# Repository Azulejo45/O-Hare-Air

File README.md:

# ┕━━O-Hare-Air━━┙ 
- Proyecto de sistema de ventilación automatizado y controlado por ESP32-C3 Super Mini. Equipado con control PWM mediante MOSFET, sensor de temperatura DS18B20 y regulación de voltaje eficiente.

### -----〈 Autores  〉-----\

> ⋆ˊˎ-Velazquez Joaquim

 ---30/09/2026---
\
\
\
### •---Especificaciones generales 
\
˚₊· ͟͟͞͞  Control de velocidad: PWM por MOSFET (IRLZ44N).\

˚₊· ͟͟͞͞  Alimentación principal: 12V / 2A (Entrada Jack DC).\

˚₊· ͟͟͞͞  Regulación interna: 5V mediante módulo Mini360.\

˚₊· ͟͟͞͞  Material de la estructura/gabinete: PLA.

_____________________________ \
\
\
.
### Objetivo del proyecto
\
El objetivo principal de este proyecto es diseñar e implementar un sistema de ventilación inteligente regulado por temperatura. Utilizando un microcontrolador ESP32-C3 Super Mini, una etapa de potencia con MOSFET y un sensor DS18B20, el sistema ajusta dinámicamente las revoluciones del ventilador de forma automática para mantener una temperatura óptima de manera eficiente.

# ⌒⌒⌒⌒⌒⌒⌒⌒┈୨•୧┈⌒⌒⌒⌒⌒⌒⌒⌒
\
\
\
\
### ˗ˏˋ ꒰ Este proyecto fue realizado con algunos componentes en donde se puede llegan a encontrar: ꒱ ˎˊ˗

 -  ESP32-C3 Super Mini.

> Memoria: 400 KB SRAM, 4 MB Flash. Conectividad: Wi-Fi (2,4 GHz).

> Bluetooth 5.0 LE (Low Energy).

> Alimentación: Funciona a 3,3 V con entrada USB-C de 5 V.

- Sensor de Temperatura: DS18B20 (KY-001).

> Voltaje de operación: 3.0V - 5.5V.

> Rango de medición: -55°C a +125°C.

-  MOSFET de Potencia: IRLZ44N.

> Tipo: Canal N (Logic-Level).

> Voltaje Drain-Source max: 55V.

> Corriente continua de Drain: 47A.

- Diodo de protección: 1N4007.

> Uso: Diodo flyback en antiparalelo con el motor para suprimir picos inductivos.

- Regulador de voltaje: Módulo Mini360.

> Tipo: Step-Down Buck Converter.

> Voltaje de entrada: 4.75V - 23V.

> Voltaje de salida ajustable: 5V.

- WS2812 (tira led x12)

> Tipo: RGB

> Uso: proyección de imagenes en el aspa

- Sensor de efecto Hall

> Uso: Medición de los rpms del motor para ayudar  los WS2812

> Alimentción: 5v con un división de tensión 3.3v para la señal de retorno

\
\
\
\
.
## ╔════╡Componentes utilizados╞════╗
➸ ESP32-C3 Super Mini.

➸ Sensor DS18B20.

➸ MOSFET IRLZ44N.

➸ Diodo 1N4007.

➸ Módulo Mini360 (Step-Down 5V).

➸ Jack DC y Borneras de conexión.

➸ Leds WS2812 (x12)

➸ Sensor efecto Hall
\
\
\
.
## Diseños de los circuitos

\

### Descripcion del funcionamiento
\
El sistema monitorea de manera constante la temperatura ambiental o del componente a través del sensor DS18B20 conectado al ESP32-C3. Mediante un algoritmo de control, el microcontrolador varía el ciclo de trabajo de la señal PWM aplicada a la compuerta (Gate) del MOSFET IRLZ44N.
De esta forma, la velocidad del ventilador de 12V aumenta o disminuye de forma proporcional a la temperatura registrada, garantizando una disipación eficiente y un funcionamiento automatizado. El diodo 1N4007 protege al circuito de las corrientes inversas generadas por el motor al apagarse o variar su velocidad.

## Esquematicos

## Layouts de PCBs

\

## Pasos a seguir para el armado del sistema

### -|Soldar los componentes en la PCB en el siguiente orden recomendado:

1. Resistencias y diodos SMD/THT (incluyendo el diodo 1N4007).

2. Borneras de conexión y Jack DC.

3. Módulo Mini360 (previamente calibrado a 5V de salida).

4. Zócalos o pines para el ESP32-C3 Super Mini y el MOSFET.

# Medidas de seguridad.
- .°-> Verifique la polaridad de la fuente de alimentación de 12V antes de conectarla al Jack DC para evitar daños en los reguladores.

-.°-> Asegúrese de que el diodo 1N4007 esté correctamente orientado (con el cátodo apuntando hacia la línea positiva de alimentación del motor).

 # -|Gabinete y Montaje 3D
Descargar el modelo 3D del soporte o gabinete ubicado en la carpeta de HARDWARE.

- Imprimir la pieza en PLA.

- Ensamblar la placa de circuito impreso dentro de la estructura junto con el ventilador y el sensor DS18B20 en la zona de medición.

## -|Código y Firmware
El código establece las lecturas del sensor de temperatura y calcula la salida PWM necesaria para gobernar el MOSFET.

Principales tareas del programa:
.°-> Lectura periódica de temperatura mediante la librería 1-Wire / DallasTemperature.
.°-> Mapeo de la temperatura leída a un rango de ciclo de trabajo PWM (0% a 100%).
.°-> Aplicación de la señal de control hacia el pin correspondiente del ESP32-C3.

## -|Compilacion/Carga
Utilice un cable USB tipo C para conectar el ESP32-C3 a un ordenador. Se recomienda utilizar el entorno de desarrollo PlatformIO o Arduino IDE.\

- Seleccione la placa ESP32-C3 Dev Module (o Super Mini equivalente) y el puerto COM correspondiente.\

- Verifique que estén instaladas las librerías necesarias para el manejo del sensor de temperatura.\

- Compile y cargue el código en el microcontrolador.

## -[Librerías principales
OneWire

DallasTemperature

## -[Datasheets/Referencias

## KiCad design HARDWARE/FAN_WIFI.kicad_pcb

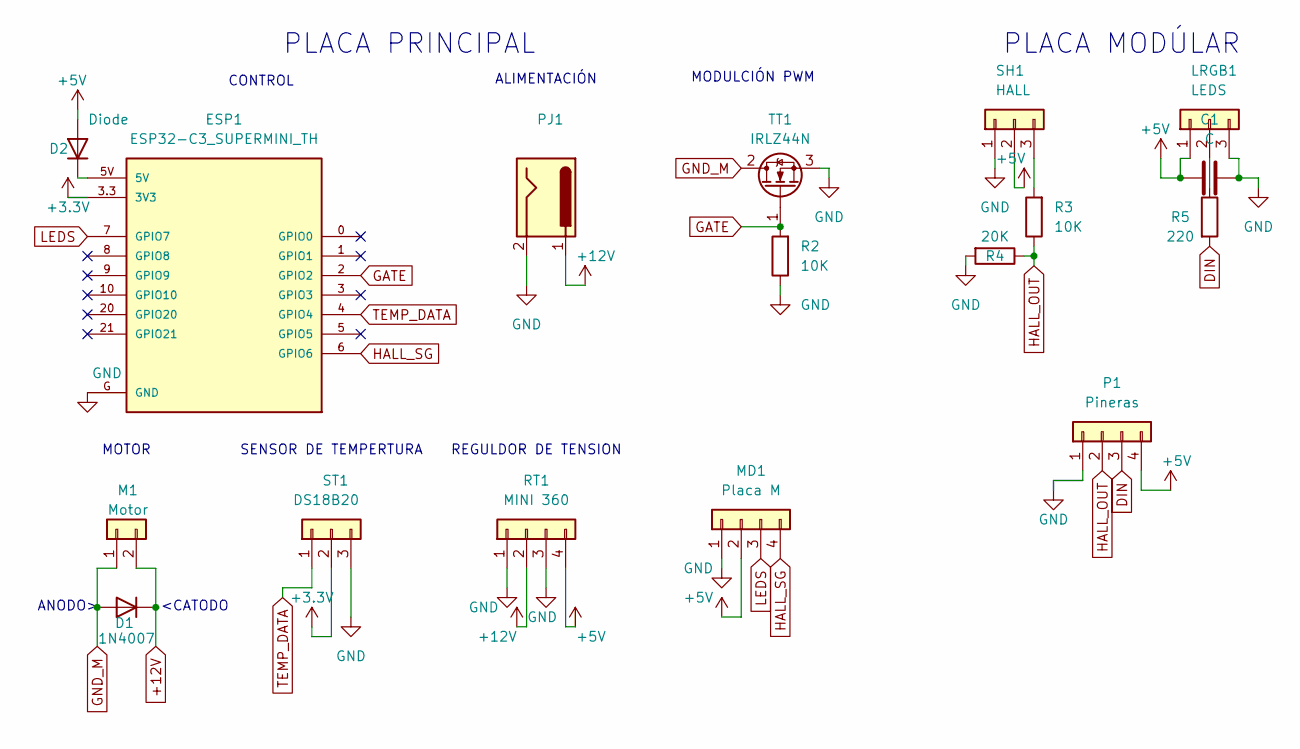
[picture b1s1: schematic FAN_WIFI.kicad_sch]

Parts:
C1: C; C_Disc_D5.0mm_W2.5mm_P5.00mm
D1: 1N4007; D_DO-41_SOD81_P10.16mm_Horizontal
D2: Diode; D_SMA
ESP1: ESP32-C3_SUPERMINI_TH; MODULE_ESP32-C3_SUPERMINI_TH
LRGB1: LEDS; PinHeader_1x03_P2.54mm_Vertical
M1: Motor; PinHeader_1x02_P2.54mm_Vertical
MD1: Placa M; PinHeader_1x04_P2.54mm_Vertical
P1: Pineras; PinHeader_1x04_P2.54mm_Vertical
PJ1: BarrelJack_CUI_PJ-063AH_Horizontal
R2: 10K; R_0805_2012Metric_Pad1.20x1.40mm_HandSolder
R3: 10K; R_Axial_DIN0204_L3.6mm_D1.6mm_P5.08mm_Horizontal
R4: 20K; R_Axial_DIN0204_L3.6mm_D1.6mm_P5.08mm_Horizontal
R5: 220; R_Axial_DIN0204_L3.6mm_D1.6mm_P5.08mm_Horizontal
RT1: MINI 360; MINI_360
SH1: HALL; PinHeader_1x03_P2.54mm_Vertical
ST1: DS18B20; PinHeader_1x03_P2.54mm_Vertical
TT1: IRLZ44N; TO-220-3_Vertical

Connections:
+3.3V: ESP1.3.3 (3V3), ST1.2
+5V: C1.1, D2.2 (A), LRGB1.1, MD1.2, P1.4, RT1.4, SH1.2
+12V: D1.1 (K), M1.2, PJ1.1, RT1.2
DIN: P1.3, R5.2
GATE: ESP1.2 (GPIO2), R2.2, TT1.1 (G)
GND: C1.2, ESP1.G (GND), LRGB1.3, MD1.1, P1.1, PJ1.2, R2.1, R4.2, RT1.1, RT1.3, SH1.1, ST1.3, TT1.3 (S)
GND_M: D1.2 (A), M1.1, TT1.2 (D)
HALL_OUT: P1.2, R3.1, R4.1
HALL_SG: ESP1.6 (GPIO6), MD1.4
LEDS: ESP1.7 (GPIO7), MD1.3
unnamed: D2.1 (K), ESP1.5V
unnamed: LRGB1.2, R5.1
unnamed: R3.2, SH1.3
TEMP_DATA: ESP1.4 (GPIO4), ST1.1

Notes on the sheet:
PLACA MODÚLAR
CONTROL
MOTOR
REGULDOR DE TENSION
<CATODO
ANODO>
PLACA PRINCIPAL
MODULCIÓN PWM
ALIMENTACIÓN
SENSOR DE TEMPERTURA

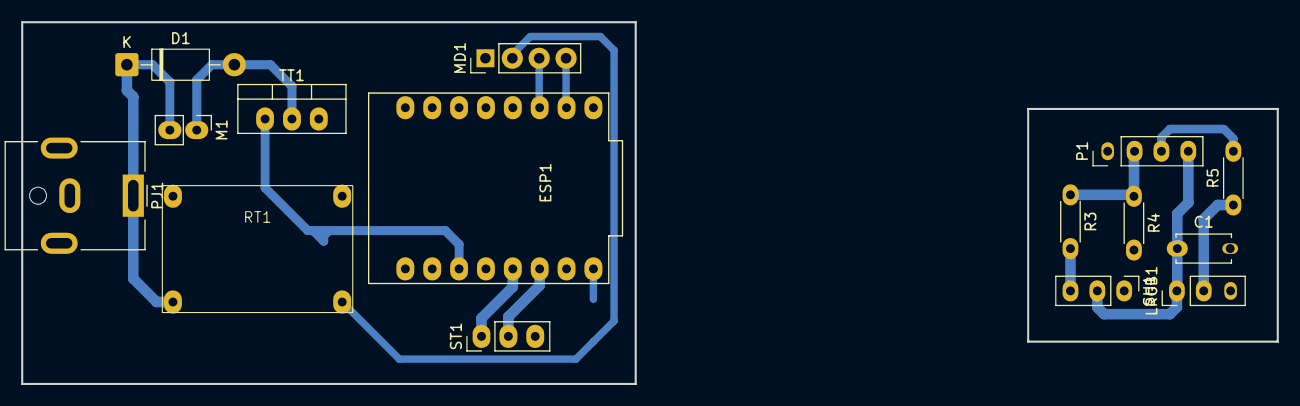
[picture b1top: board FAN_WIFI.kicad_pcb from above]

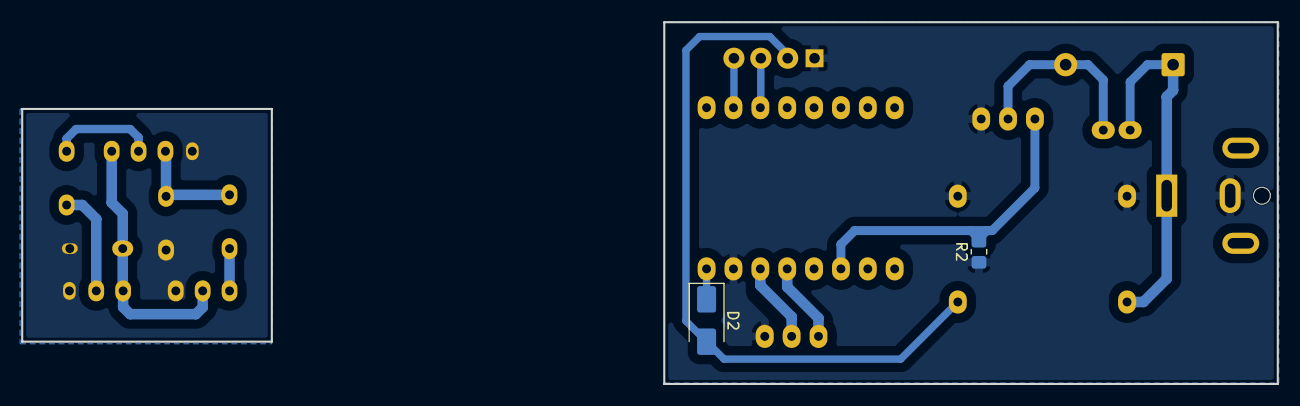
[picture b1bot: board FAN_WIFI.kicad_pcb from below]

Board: 2 copper layers, 118.7 x 34.2 mm, 17 parts (2 on the bottom side), 14 nets.
